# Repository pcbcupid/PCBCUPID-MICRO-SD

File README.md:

# GMOD-MICRO-SD

This repo contains open source PCB files for PCBCUPID GMOD MicroSD <br/>
This particular PCB is designed using Kicad v9.0

**This design has been built and tested successfully!**
For more details, check out the product pages at

   * [Gmod-Micro-SD](https://shop.pcbcupid.com/product/gm003/)
   * [Docs](https://learn.pcbcupid.com/boards/g-mod/micro-sd)

We are here to build India's largest open source hardware community, If you like to support
please consider buying the product from the above link!

[Creative Commons Attribution, Share-Alike license](https://creativecommons.org/licenses/by-sa/4.0/deed.en)
All text above must be included in any redistribution

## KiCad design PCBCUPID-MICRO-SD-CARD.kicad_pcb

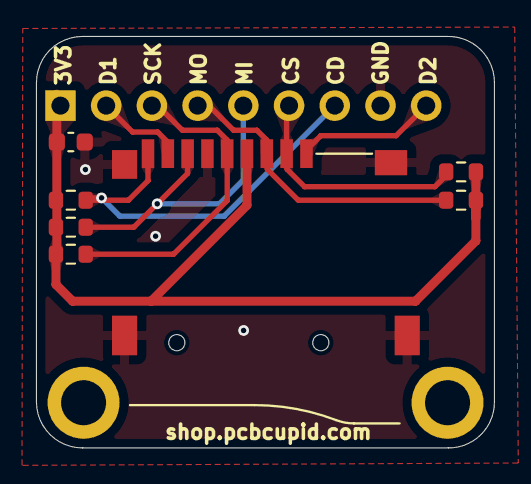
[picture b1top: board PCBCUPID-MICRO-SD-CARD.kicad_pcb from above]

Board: 2 copper layers, 25.4 x 22.9 mm, 8 parts (0 on the bottom side), 9 nets.

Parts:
C1: 0.1uF; C_0603_1608Metric
J1: Micro_SD_Card_Det1; SUNTECH_ST-TF-003A
J2: Conn_01x09; PinHeader_1x09_P2.54mm_Vertical
R1, R3, R4, R5, R6: 10K; R_0603_1608Metric

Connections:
+3V3: C1.1, J1.4 (VDD), J2.1, R1.2, R3.1, R4.1, R5.1, R6.1
/CD: J1.9 (DET), J2.7, R1.1
/CS: J1.2 (DAT3/CD), J2.6, R6.2
/D1: J1.8 (DAT1), J2.2
/D2: J1.1 (DAT2), J2.9
/MISO: J1.7 (DAT0), J2.5, R3.2
/MOSI: J1.3 (CMD), J2.4, R5.2
/SCK: J1.5 (CLK), J2.3, R4.2
GND: C1.2, J1.6 (VSS), J1.10 (SHIELD), J2.8

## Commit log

2025-06-28 Initial Upload
